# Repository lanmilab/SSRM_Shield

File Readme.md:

# IoT Solid State Ralay and Power Monitor Shield

Shield made specifically for Arduino nano IoT or compatible development board.
- Based on triac transistor with opto-isolated driving to be used for heater or lighting control IoT applications.
- Isolated 2Watts AC/DC converter.
- Integrates AC power monitor ACS71020KMABTR-030B3-I2C.
- One on board NTC temperature sensor, plus header for off-board NTC. 

## License

KiCad design is available but not verified, use on your own resposibility!

THE DESIGN IS PROVIDED "AS IS" AND THE AUTHOR DISCLAIMS ALL WARRANTIES WITH REGARD TO THIS DESIGN INCLUDING ALL IMPLIED WARRANTIES OF MERCHANTABILITY AND FITNESS. IN NO EVENT SHALL THE AUTHOR BE LIABLE FOR ANY SPECIAL, DIRECT, INDIRECT, OR CONSEQUENTIAL DAMAGES OR ANY DAMAGES WHATSOEVER RESULTING FROM LOSS OF USE, DATA OR PROFITS, WHETHER IN AN ACTION OF CONTRACT, NEGLIGENCE OR OTHER TORTIOUS ACTION, ARISING OUT OF OR IN CONNECTION WITH THE USE OR PERFORMANCE OF THIS DESIGN.

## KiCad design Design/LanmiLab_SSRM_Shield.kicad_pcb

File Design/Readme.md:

# IoT Solid State Ralay and Power Monitor Shield KiCad Design Files

Gerber and assembly files available in Outputs directory.

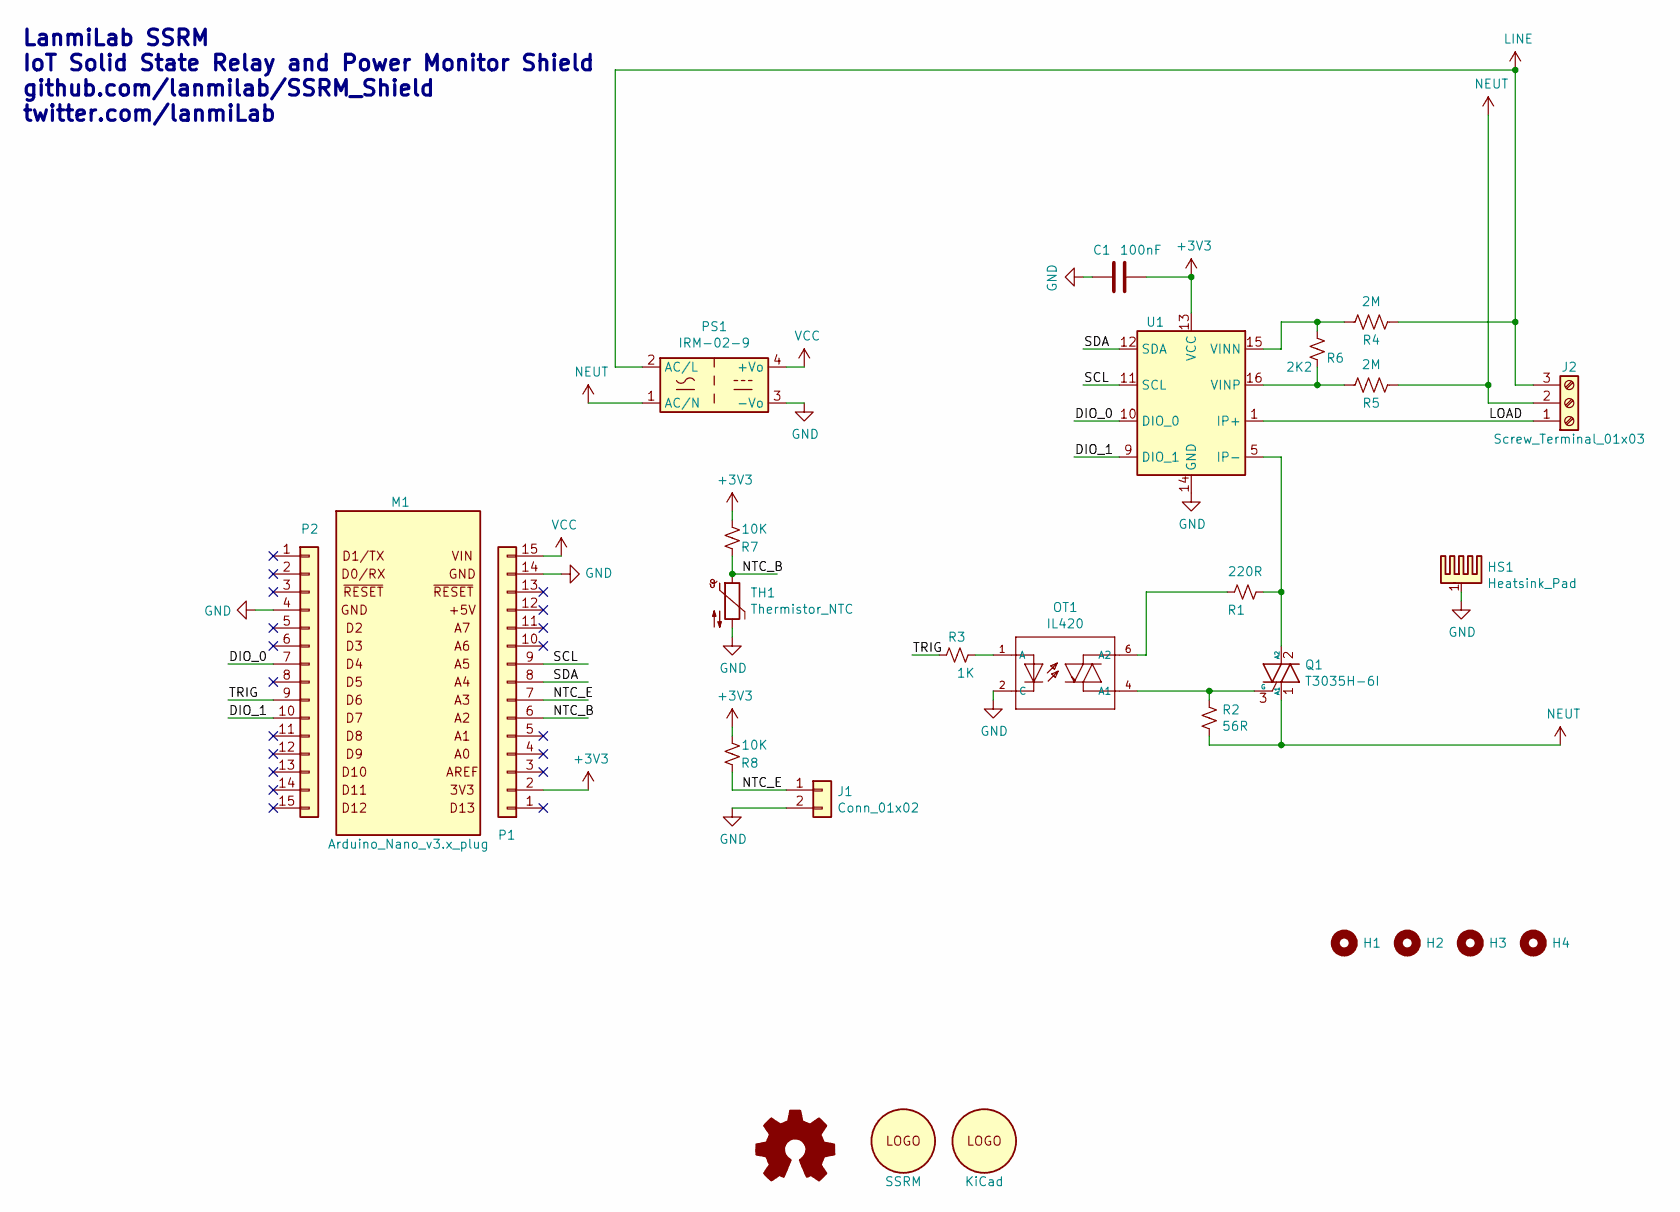
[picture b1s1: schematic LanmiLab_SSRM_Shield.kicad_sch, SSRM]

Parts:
C1: 100nF; C_Disc_D3.4mm_W2.1mm_P2.50mm; Part Number K104K15X7RF53L2
H1, H2, H3, H4: MountingHole; MountingHole_2.7mm_M2.5
HS1: Heatsink_Pad; Heatsink_Fischer_SK129-STS_42x25mm_2xDrill2.5mm; Part Number FA-T220-25E
J1: Conn_01x02; PinHeader_1x02_P2.54mm_Vertical; Part Number M20-9990245
J2: Screw_Terminal_01x03; TerminalBlock_MetzConnect_Type073_RT02603HBLU_1x03_P5.08mm_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; Part Number MKDS 3/ 3-5,08
LOGO1: Logo_Open_Hardware_Small; OSHW-Logo2_9.8x8mm_SilkScreen
LOGO2: SSRM; ssr
LOGO3: KiCad; KiCad-Logo2_5mm_SilkScreen
M1: Arduino_Nano_v3.x_plug; Arduino_Nano_33_IoT_3D_NoPads
OT1: IL420; DIP-6_W7.62mm_LongPads; Part Number IL420
P1, P2: Conn_01x15; PinSocket_1x15_P2.54mm_Vertical; Part Number PPPC151LFBN-RC
PS1: IRM-02-9; Converter_ACDC_MeanWell_IRM-02-xx_THT; Part Number IRM-02-9
Q1: T3035H-6I; TO-220-3_Vertical; Part Number T3035H-6I
R1: 220R; R_Axial_DIN0207_L6.3mm_D2.5mm_P7.62mm_Horizontal; Part Number MFP1-220R JI
R2: 56R; R_Axial_DIN0207_L6.3mm_D2.5mm_P7.62mm_Horizontal; Part Number MRS25000C5609FCT00
R3: 1K; R_Axial_DIN0204_L3.6mm_D1.6mm_P5.08mm_Horizontal; Part Number LR0204F1K0
R4, R5: 2M; R_Axial_DIN0414_L11.9mm_D4.5mm_P15.24mm_Horizontal; Part Number HVR3700002004FR500
R6: 2K2; R_Axial_DIN0204_L3.6mm_D1.6mm_P5.08mm_Horizontal; Part Number CFR16J2K2
R7, R8: 10K; R_Axial_DIN0204_L3.6mm_D1.6mm_P5.08mm_Horizontal; Part Number CFR16J10K
TH1: Thermistor_NTC; C_Disc_D3.8mm_W2.6mm_P2.50mm; Part Number B57891M0103K000
U1: ACS71020KMABTR-030B3-I2C; SOIC-16W_7.5x10.3mm_P1.27mm; Part Number ACS71020KMABTR-030B3-I2C

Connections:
+3V3: C1.1, P1.2, R7.2, R8.2, U1.13 (VCC)
/DIO_0: P2.7, U1.10 (DIO_0)
/DIO_1: P2.10, U1.9 (DIO_1)
/LOAD: J2.1, U1.1 (IP+), U1.2 (IP+), U1.3 (IP+), U1.4 (IP+)
/NTC_B: P1.6, R7.1, TH1.1
/NTC_E: J1.1, P1.7, R8.1
/SCL: P1.9, U1.11 (SCL)
/SDA: P1.8, U1.12 (SDA)
/TRIG: P2.9, R3.1
GND: C1.2, HS1.1, J1.2, OT1.2 (C), P1.14, P2.4, PS1.3 (-Vo), TH1.2, U1.14 (GND)
LINE: J2.3, PS1.2 (AC/L), R4.1
NEUT: J2.2, PS1.1 (AC/N), Q1.1 (A1), R2.2, R5.1
unnamed: OT1.1 (A), R3.2
unnamed: OT1.4 (A1), Q1.3 (G), R2.1
unnamed: OT1.6 (A2), R1.2
unnamed: Q1.2 (A2), R1.1, U1.5 (IP-), U1.6 (IP-), U1.7 (IP-), U1.8 (IP-)
unnamed: R4.2, R6.1, U1.15 (VINN)
unnamed: R5.2, R6.2, U1.16 (VINP)
VCC: P1.15, PS1.4 (+Vo)

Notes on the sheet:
LanmiLab SSRM IoT Solid State Relay and Power Monitor Shield github.com/lanmilab/SSRM_Shield twitter.com/lanmiLab

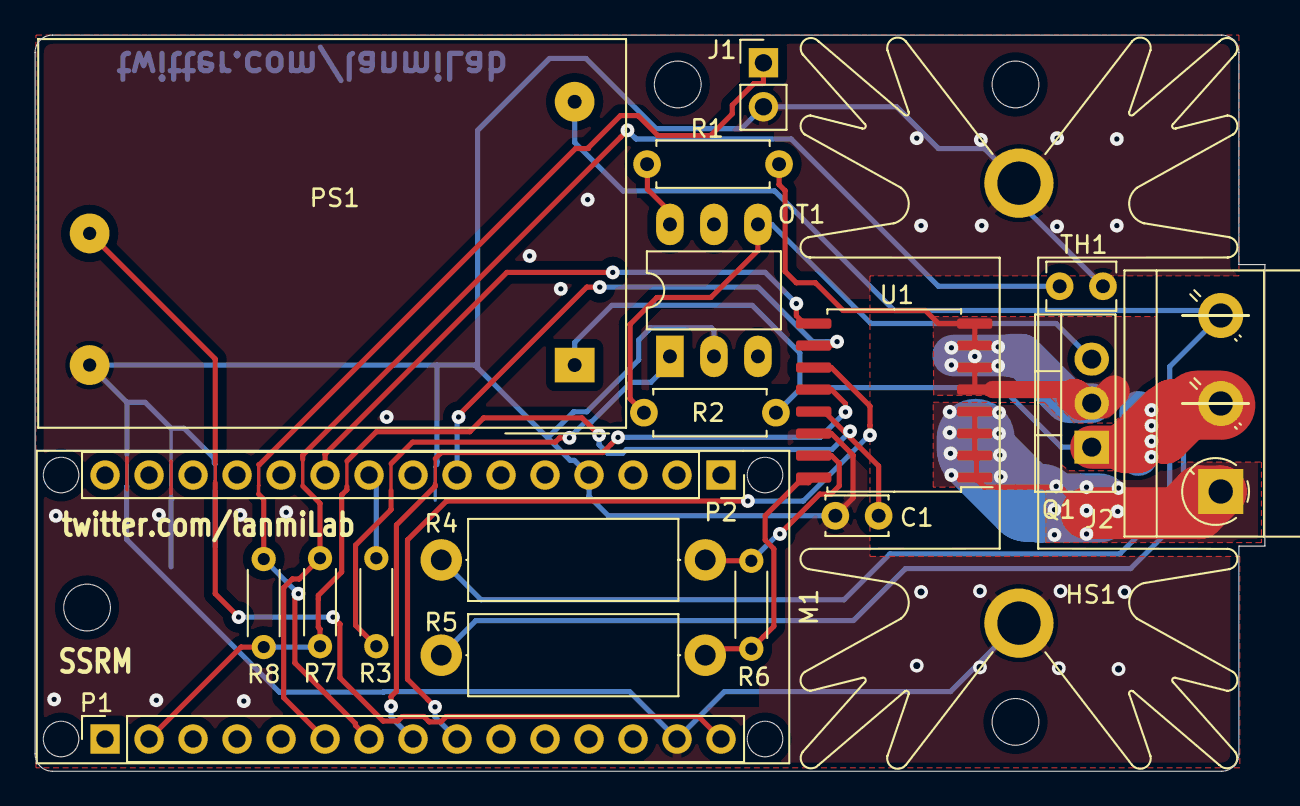
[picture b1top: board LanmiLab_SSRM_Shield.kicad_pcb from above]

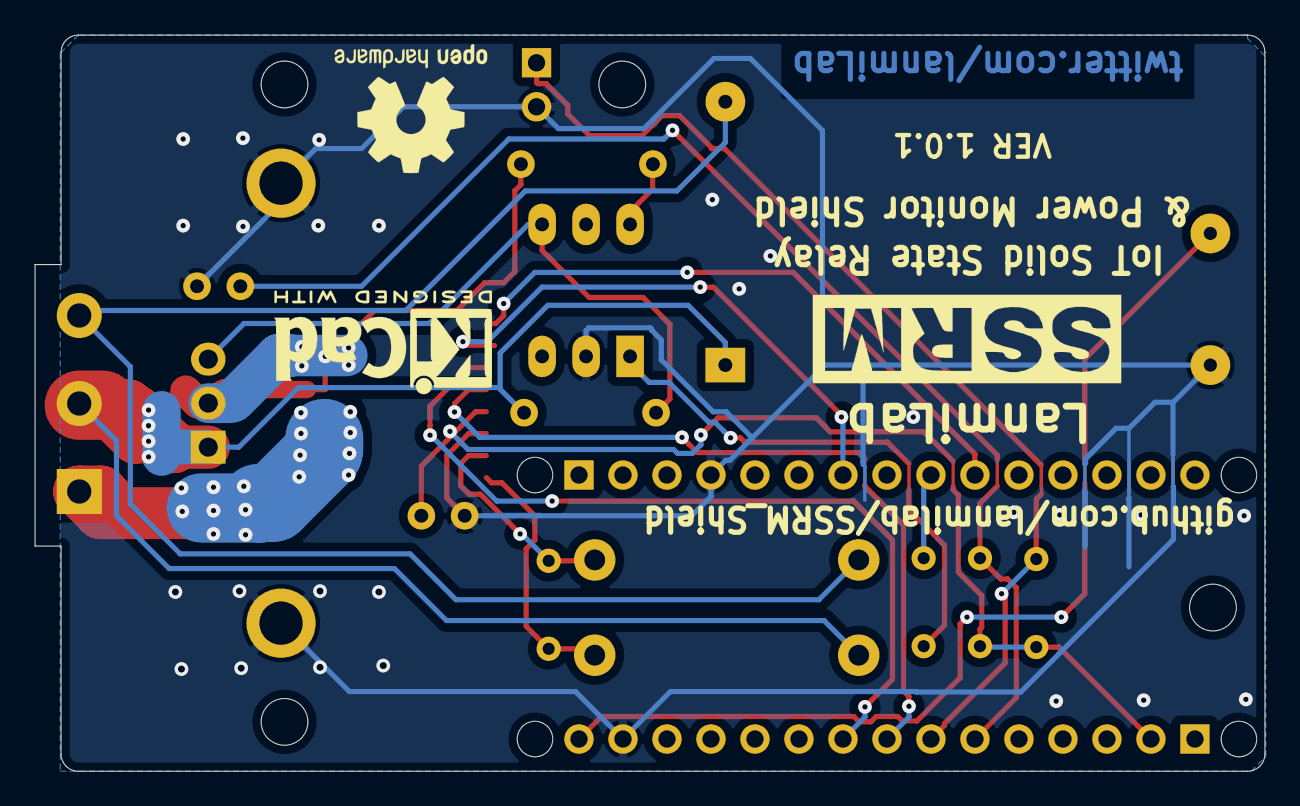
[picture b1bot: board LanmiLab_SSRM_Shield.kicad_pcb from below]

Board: 2 copper layers, 71.0 x 42.5 mm, 27 parts (3 on the bottom side), 19 nets.

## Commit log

2022-02-19 Initial commit V1.0.1
